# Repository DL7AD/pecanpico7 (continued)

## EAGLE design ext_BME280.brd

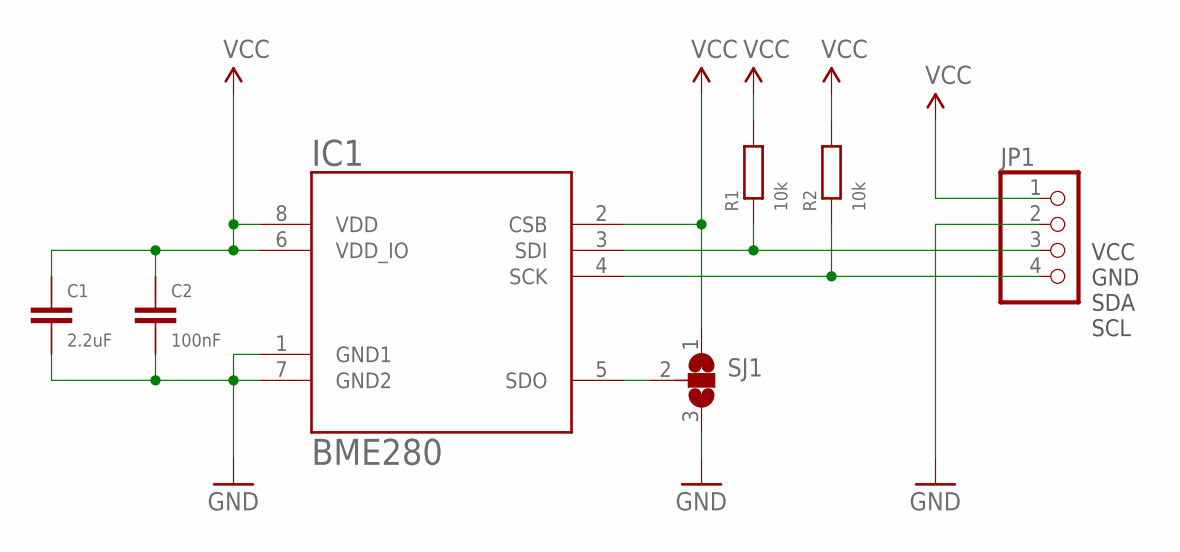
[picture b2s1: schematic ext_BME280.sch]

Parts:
C1: 2.2uF; 0402
C2: 100nF; 0402
IC1: BME280; BME280_BME280
JP1: PINHD-1X4; 1X04
R1, R2: 10k; 0402
SJ1: SJ2W; SJ_2

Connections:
GND: C1.P$1 (1), C2.P$1 (1), IC1.1 (GND1), IC1.7 (GND2), JP1.2, SJ1.3
unnamed: IC1.5 (SDO), SJ1.2
unnamed: IC1.3 (SDI), JP1.3, R1.P$1 (1)
unnamed: IC1.4 (SCK), JP1.4, R2.P$1 (1)
VCC: C1.P$2 (2), C2.P$2 (2), IC1.2 (CSB), IC1.6 (VDD_IO), IC1.8 (VDD), JP1.1, R1.P$2 (2), R2.P$2 (2), SJ1.1

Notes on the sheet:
VCC GND SDA SCL

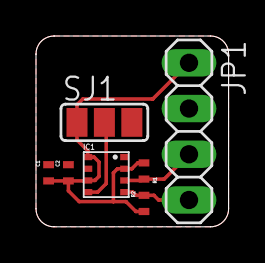
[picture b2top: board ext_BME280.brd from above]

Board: 2 copper layers, 10.7 x 10.6 mm, 7 parts (0 on the bottom side), 5 nets.

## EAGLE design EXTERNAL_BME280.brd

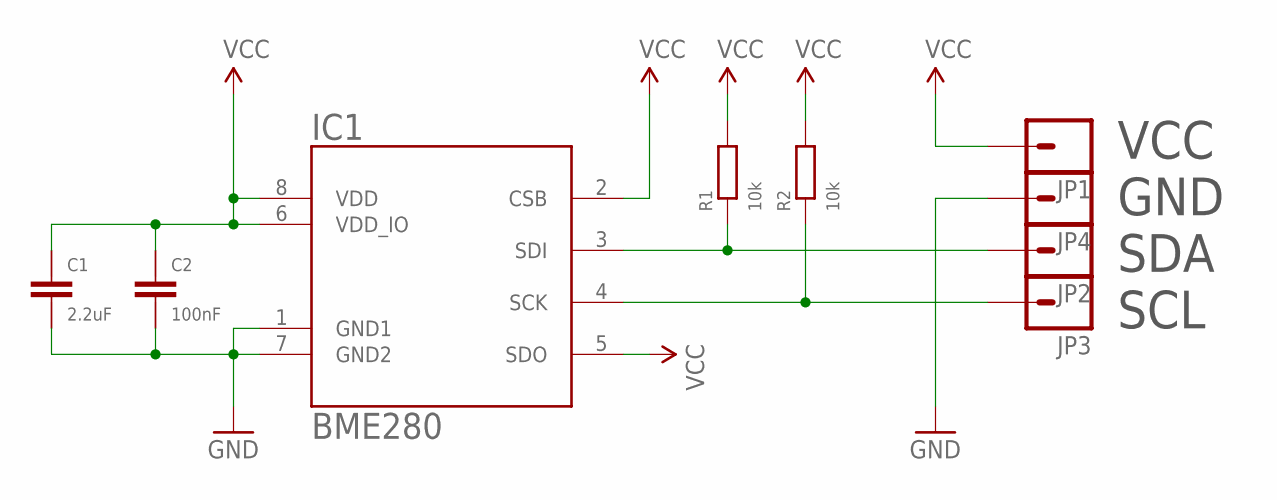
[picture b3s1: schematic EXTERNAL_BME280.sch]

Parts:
C1: 2.2uF; 0402
C2: 100nF; 0402
IC1: BME280
JP1, JP2, JP3, JP4: M01SOLAR; PAD2_1.8X0.9
R1, R2: 10k; 0402

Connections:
GND: C1.P$1 (1), C2.P$1 (1), IC1.1 (GND1), IC1.7 (GND2), JP4.1
unnamed: IC1.3 (SDI), JP2.1, R1.P$1 (1)
unnamed: IC1.4 (SCK), JP3.1, R2.P$1 (1)
VCC: C1.P$2 (2), C2.P$2 (2), IC1.2 (CSB), IC1.5 (SDO), IC1.6 (VDD_IO), IC1.8 (VDD), JP1.1, R1.P$2 (2), R2.P$2 (2)

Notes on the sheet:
VCC GND SDA SCL

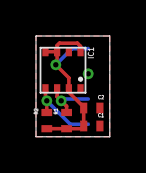
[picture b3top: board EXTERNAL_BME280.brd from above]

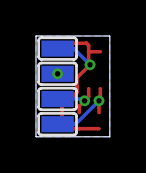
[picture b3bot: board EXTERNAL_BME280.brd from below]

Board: 2 copper layers, 4.1 x 5.6 mm, 9 parts (4 on the bottom side), 4 nets.

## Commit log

2015-10-28 Added BME280 breakout board
2015-10-28 Enlarged BME280 breakout board
2015-10-28 Removed temp files
2015-10-29 Added Pecan, 2xSi4464, ublox MAX7/8, STM32F427
2015-10-29 Renamed external BME280 board
2015-10-29 Connected parts
2015-10-30 Added SDRAM and routed, Added camera pins
2015-10-30 Add probably useless files
2015-10-30 Removed useless files
2015-10-30 Moved parts around
2015-10-30 Moved parts around mainly, changed pinheaders, added busses
2015-10-31 Added power management
2015-10-31 Added gitignore for temp files
2015-10-31 Reordered power supply components
2015-10-31 Moved components around
2015-11-01 Fixed all DRC errors
2015-11-01 Rerouted signals
2015-11-01 Added LDO's
2015-11-19 Done many things Added camera header Removed SDRAM Moved parts around
2015-11-20 Added PA for Radio 1 and voltag REF
2015-11-20 Resolved DRC errors
2015-11-21 Added RF6886, moved parts around
2015-11-21 Connected ADCs
2015-11-21 Connected GPS to STM32F4, moved parts around
2015-11-22 Many changes Added REF pullups to PA Added SD card slot Added MOSFET for SD card and camera Added Status LEDS Added capacitors for PA_PWR_REF and PA_PWR_REV Added Debug UART output Added UART to GPS 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
2015-11-22 Connected LED pins to pinheader
2015-11-23 Added GPS preamplifier
2015-11-23 Fixed impedance errors
2015-11-23 Fixed DRC errors
2015-11-23 Added MPU9250
2015-11-23 Connected GNDs
2015-11-24 Fixed errors Fixed wrong connected DCMI pins Fixed missing I2C pull ups Fixed missing voltage dividers at ADC
2015-11-26 Fixed errors, moved parts around Fixed GPS BIAS preamp connection Corrected GND polygons Added NRST pullup Added BYPASS_REG pullup Implemented I2C pullups for camera Checked all label connections to 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
2015-11-26 Removed SD MOSFET, Added VSOL pad
2015-11-26 Tidy up
2015-11-27 Done many things Replaced 0402 sense resistors by 0603 Fixed LPF at Radio 2 Connected Radio 1 PA to VBAT instead of VCC Corrected MPU9250 GND pad Relocated VBAT signal to avoid interference to MPU925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
2015-11-27 Added switching SJ to battery
2015-11-27 Fixed GPS preamp VCC connection
2015-11-27 Added photos
2015-11-28 Improved GND connections
2015-11-28 Improved wiring
2015-11-28 Done many things Added solar GND pads Added names to components Done on-board documentation
2015-11-29 Fixed camera connection, tidy up
2015-11-29 Added schematic picture
2015-11-29 Added Gerbers
2015-11-29 Fixed text positions
2015-11-29 Moved silkscreen
2015-11-29 Updated GERBER
2015-12-03 Fixed incorrect voltage supply at OV2640
2015-12-10 Relocated names, added infos, added PCB name
2015-12-10 Adjusted symbols
2015-12-11 Moved Silkscreen, improved GND-connections
2015-12-12 Updated sch and brd images
2015-12-12 Moved files
2015-12-12 Created documentation
2015-12-13 Fixed camera name
2015-12-14 Added error notes
2015-12-14 Adjusted values
2015-12-17 Renamed components
2015-12-23 Added production images
2015-12-27 Adjusted preR of LEDs and voltage divider of TPS62260
2015-12-27 Added PCB errors and warnings
2015-12-30 Fixed errors, improved routing Fixed: LED's switched on in sleep Fixed: Solder on solder jumper Fixed: Pad incredible close to each other at SPU9250 and PAC1720 Fixed: BYPASS connected to VCC
2016-01-05 Moved BME280
2016-01-23 Implemented multiple switching regulators, moved parts around
2016-02-06 Added new error
2016-02-09 Moved parts around, removed SD SPI
2016-02-09 Moved all components to the top layer
2016-02-09 Connected SD slot
2016-02-10 Added 1.3V LDO for camera
2016-02-11 Connected GNDs, inserted LPF to PA VREG
2016-02-11 Moved parts around, resolved DRC errors
2016-02-11 Added micro SD card slot
2016-02-11 Removed wires and exposed pad from MPU9250
2016-02-12 Moved parts around, changed MCU GPIO connections
2016-02-12 Moved camera solder jumper
2016-02-16 Changed position of radio 1 and 2
2016-02-17 Moved parts around, changed values of filters
2016-02-18 Changed switching regulators, moved parts around
2016-02-18 Removed PA switch MOSFET, moved parts around
2016-02-18 Removed DRC errors
2016-02-18 Added defaults to solder jumper
2016-02-23 Added switching regulator for PA
2016-02-24 Moved all parts in place
2016-03-04 Done many things Changed 2.5V switching regulators to LDOs Connected Si4464 GPIOs and CS Removed GND at LPF Removed MPU9250 Moved parts around
2016-03-04 Checked all pins, DRC, adjusted Silkscreen, checked VCC trace width
2016-03-04 Adjusted silkscreen, created GERBERs, updated CAM script
2016-03-05 Moved parts around, updated GERBER
2016-03-18 Connected TCXO to STM32_OSC pin
2016-03-21 Replaced small TCXO package to larger one
2016-03-21 Connected radio GPIOs to one UART TX
2016-03-22 Modified voltage supply of camera
2016-03-22 Added Polygons for MCU
2016-03-22 Added decoupling capacitor
2016-03-23 Connected LED4 to MCU pin, added GND cutout
2016-03-27 Done many things Added mounting point for camera Replaced 1X4 pin header with 2X4 pinheader (I2C header) Added battery and solar jumper Added voltage divider for Vsolar Removed 100mil mounting point
2016-03-28 Moved silkscreen, updated GERBERs
2016-03-28 Updated GERBER ZIP file
2016-03-28 Increased size of I2C header
2016-03-28 Updated GERBERs
2016-03-28 Removed old export files
2016-03-29 Tidy up schematic file
2016-03-29 Tidy up schematic file2
